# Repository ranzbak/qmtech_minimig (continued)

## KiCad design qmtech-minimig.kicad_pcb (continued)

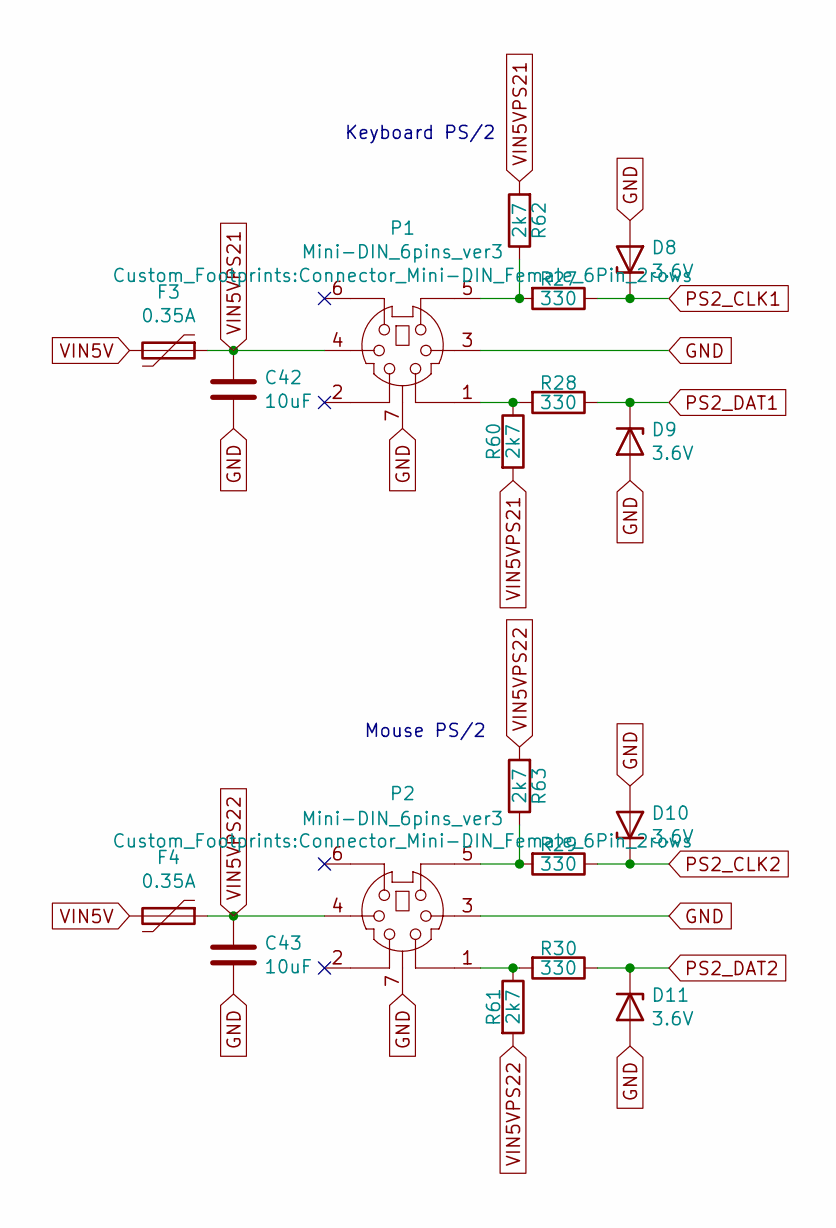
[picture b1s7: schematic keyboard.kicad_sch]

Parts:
C42, C43: 10uF; C_0805_2012Metric
D8, D9, D10, D11: 3.6V; D_SOD-323_HandSoldering
F3, F4: 0.35A; Fuse_0805_2012Metric
P1, P2: Mini-DIN_6pins_ver3; Connector_Mini-DIN_Female_6Pin_2rows
R27, R28, R29, R30: 330; R_0603_1608Metric
R60, R61, R62, R63: 2k7; R_0603_1608Metric

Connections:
unnamed: P1.1, R28.2, R60.1
unnamed: P1.5, R27.2, R62.1
unnamed: P2.1, R30.2, R61.1
unnamed: P2.5, R29.2, R63.1
PS2_CLK1: D8.1 (K), R27.1; also elsewhere on the board
PS2_CLK2: D10.1 (K), R29.1; also elsewhere on the board
PS2_DAT1: D9.1 (K), R28.1; also elsewhere on the board
PS2_DAT2: D11.1 (K), R30.1; also elsewhere on the board
VIN5V: F3.2, F4.2; also elsewhere on the board
VIN5VPS21: C42.1, F3.1, P1.4, R60.2, R62.2
VIN5VPS22: C43.1, F4.1, P2.4, R61.2, R63.2

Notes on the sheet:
Mouse PS/2
Keyboard PS/2

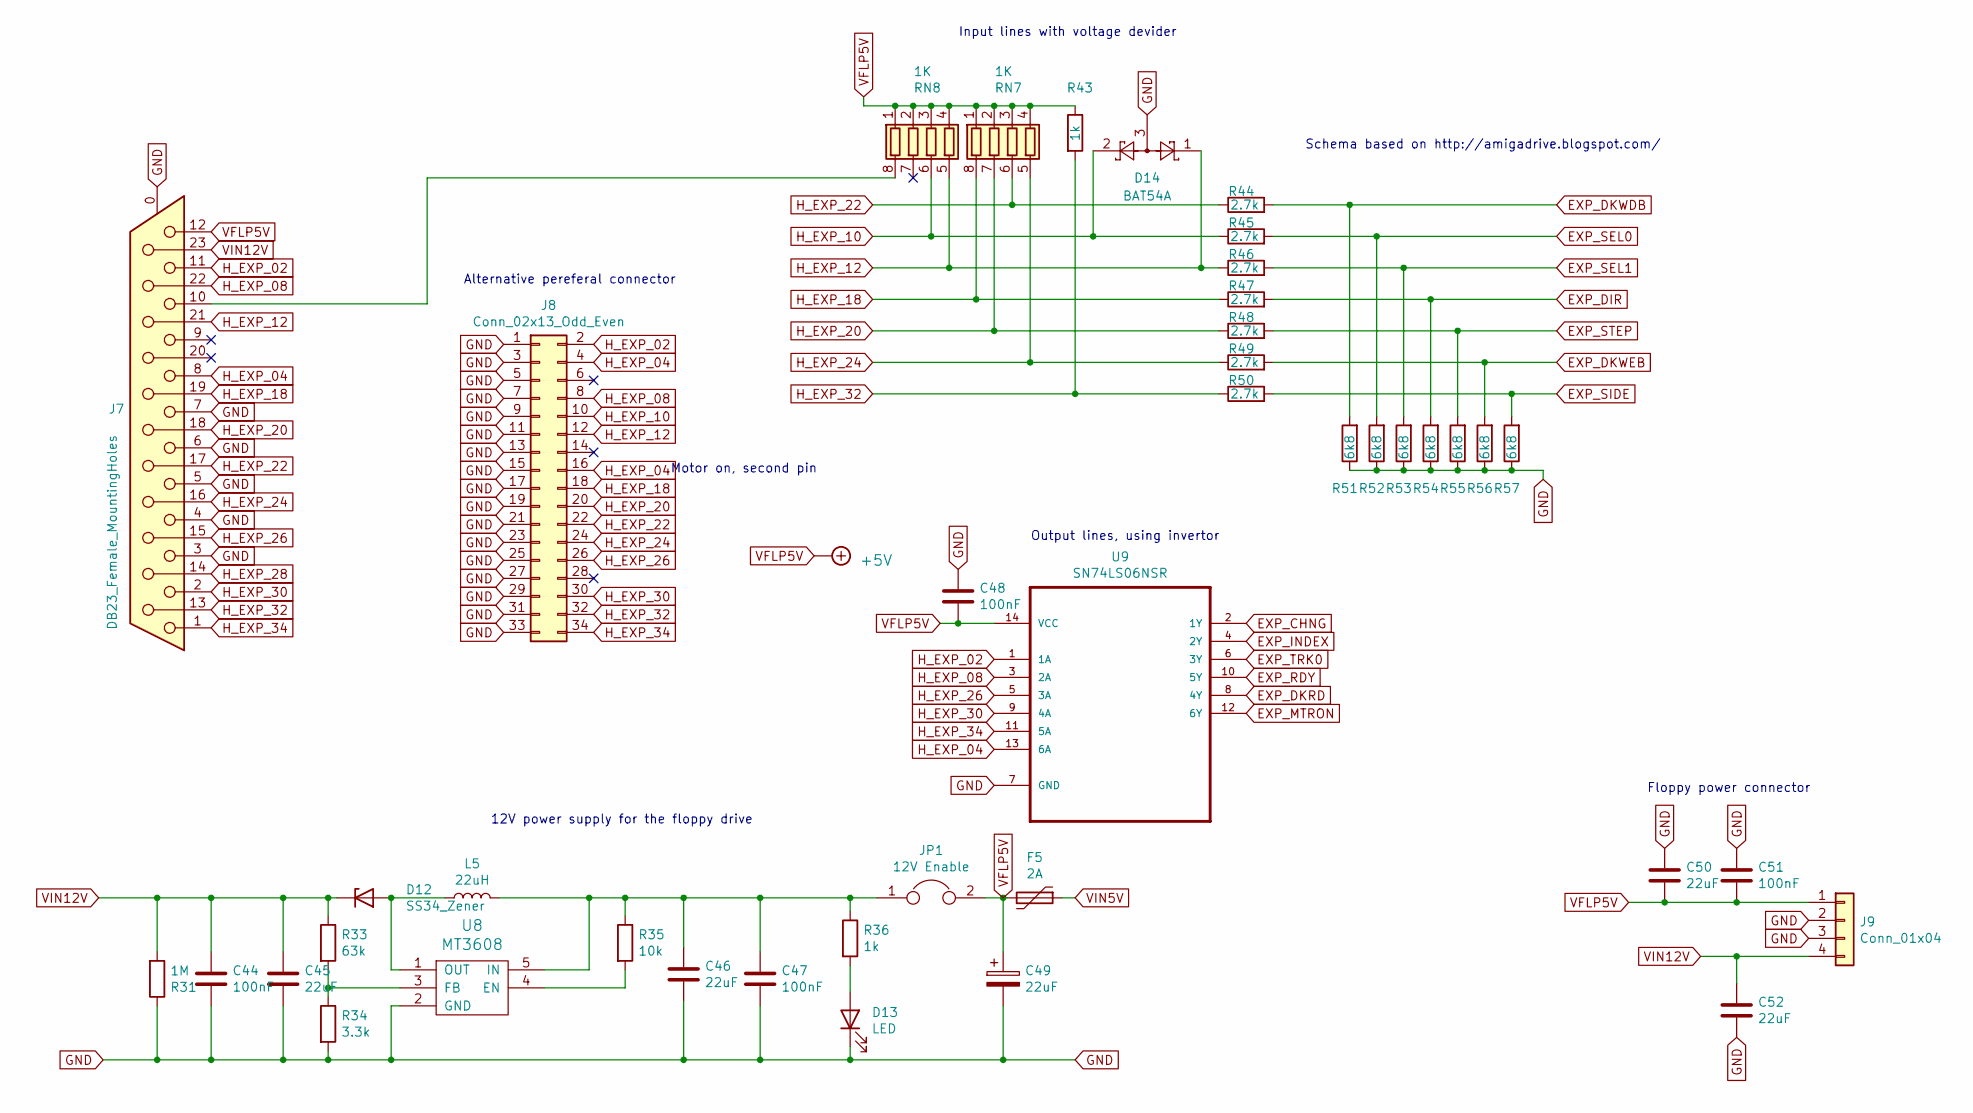
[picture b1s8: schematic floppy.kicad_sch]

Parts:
C44, C47, C48, C51: 100nF; C_0603_1608Metric
C45, C46, C50, C52: 22uF; C_0805_2012Metric
C49: 22uF; CP_Elec_5x5.4
D12: SS34_Zener; D_SMC
D13: LED; LED_0603_1608Metric
D14: BAT54A; SOT-23
F5: 2A; Fuse_0805_2012Metric
J7: DB23_Female_MountingHoles; DSUB-23_Female_Horizontal_P2.77x2.84mm_EdgePinOffset7.70mm_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
J8: Conn_02x13_Odd_Even; PinHeader_2x17_P2.54mm_Vertical
J9: Conn_01x04; JST-4-PTH-VERT
JP1: 12V Enable; PinHeader_1x02_P2.54mm_Vertical
L5: 22uH; L_10.4x10.4_H4.8
R31: 1M; R_0603_1608Metric
R33: 63k; R_0603_1608Metric
R34: 3.3k; R_0603_1608Metric
R35: 10k; R_0603_1608Metric
R36, R43: 1k; R_0603_1608Metric
R44, R45, R46, R47, R48, R49, R50: 2.7k; R_0603_1608Metric
R51, R52, R53, R54, R55, R56, R57: 6k8; R_0603_1608Metric
RN7, RN8: 1K; R_Array_Convex_4x0603
U8: MT3608; SOT-23-6
U9: SN74LS06NSR; SOIC127P780X200-14N

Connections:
EXP_CHNG: U9.2 (1Y); also elsewhere on the board
EXP_DIR: R47.2, R54.2; also elsewhere on the board
EXP_DKRD: U9.8 (4Y); also elsewhere on the board
EXP_DKWDB: R44.2, R51.2; also elsewhere on the board
EXP_DKWEB: R49.2, R56.2; also elsewhere on the board
EXP_INDEX: U9.4 (2Y); also elsewhere on the board
EXP_MTRON: U9.12 (6Y)
EXP_RDY: U9.10 (5Y); also elsewhere on the board
EXP_SEL0: R45.2, R52.2; also elsewhere on the board
EXP_SEL1: R46.2, R53.2; also elsewhere on the board
EXP_SIDE: R50.2, R57.2; also elsewhere on the board
EXP_STEP: R48.2, R55.2; also elsewhere on the board
EXP_TRK0: U9.6 (3Y); also elsewhere on the board
H_EXP_02: J7.11, J8.2, U9.1 (1A)
H_EXP_04: J7.8, J8.4, J8.16, U9.13 (6A)
H_EXP_08: J7.22, J8.8, U9.3 (2A)
H_EXP_18: J7.19, J8.18, R47.1, RN7.8 (R1.2); also elsewhere on the board
H_EXP_20: J7.18, J8.20, R48.1, RN7.7 (R2.2); also elsewhere on the board
H_EXP_22: J7.17, J8.22, R44.1, RN7.6 (R3.2); also elsewhere on the board
H_EXP_24: J7.16, J8.24, R49.1, RN7.5 (R4.2); also elsewhere on the board
H_EXP_26: J7.15, J8.26, U9.5 (3A)
H_EXP_28: J7.14
H_EXP_30: J7.2, J8.30, U9.9 (4A)
H_EXP_32: J7.13, J8.32, R43.2, R50.1
H_EXP_34: J7.1, J8.34, U9.11 (5A)
unnamed: C46.1, C47.1, JP1.1, L5.2, R35.1, R36.1, U8.5 (IN)
unnamed: D12.2 (A), L5.1, U8.1 (OUT)
unnamed: D13.2 (A), R36.2
unnamed 145: J7.10, RN8.8 (R1.2); also elsewhere on the board
unnamed: R33.2, R34.1, U8.3 (FB)
unnamed: R35.2, U8.4 (EN)
VFLP5V: C48.2, C49.1, C50.2, C51.2, F5.2, J7.12, J9.1, JP1.2, R43.1, RN7.1 (R1.1), RN7.2 (R2.1), RN7.3 (R3.1), RN7.4 (R4.1), RN8.1 (R1.1), RN8.2 (R2.1), RN8.3 (R3.1), RN8.4 (R4.1), U9.14 (VCC); also elsewhere on the board
VIN5V: F5.1; also elsewhere on the board
VIN12V: C44.1, C45.1, C52.1, D12.1 (K), J7.23, J9.4, R31.2, R33.1

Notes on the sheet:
Alternative pereferal connector
Motor on, second pin
Output lines, using invertor
Floppy power connector
Input lines with voltage devider
Schema based on http://amigadrive.blogspot.com/
12V power supply for the floppy drive

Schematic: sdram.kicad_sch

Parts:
C53, C54, C56, C57, C59, C60: 100nF; C_0603_1608Metric
C55, C58, C61: 10nF; C_0603_1608Metric
C62, C63: 10uF; C_0805_2012Metric
IC1: AS4C16M16SA-6TCN; SOP80P1176X120-54N; Manufacturer_Part_Number AS4C16M16SA-6TCN; Mouser Part Number 913-4C16M16SA-6TCN

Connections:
3V3: C53.1, C54.1, C55.1, C56.1, C57.1, C58.1, C59.1, C60.1, C61.1, C62.1, C63.1, IC1.1 (VDD_1), IC1.3 (VDDQ_1), IC1.9 (VDDQ_2), IC1.14 (VDD_2), IC1.27 (VDD_3), IC1.43 (VDDQ_3), IC1.49 (VDDQ_4); also elsewhere on the board
SDRAM_A0: IC1.23 (A0); also elsewhere on the board
SDRAM_A1: IC1.24 (A1); also elsewhere on the board
SDRAM_A2: IC1.25 (A2); also elsewhere on the board
SDRAM_A3: IC1.26 (A3); also elsewhere on the board
SDRAM_A4: IC1.29 (A4); also elsewhere on the board
SDRAM_A5: IC1.30 (A5); also elsewhere on the board
SDRAM_A6: IC1.31 (A6); also elsewhere on the board
SDRAM_A7: IC1.32 (A7); also elsewhere on the board
SDRAM_A8: IC1.33 (A8); also elsewhere on the board
SDRAM_A9: IC1.34 (A9); also elsewhere on the board
SDRAM_A10: IC1.22 (A10/AP); also elsewhere on the board
SDRAM_A11: IC1.35 (A11); also elsewhere on the board
SDRAM_A12: IC1.36 (A12); also elsewhere on the board
SDRAM_BA0: IC1.20 (BA0); also elsewhere on the board
SDRAM_BA1: IC1.21 (BA1); also elsewhere on the board
SDRAM_CAS: IC1.17 (CAS#); also elsewhere on the board
SDRAM_CKE: IC1.37 (CKE); also elsewhere on the board
SDRAM_CLK: IC1.38 (CLK); also elsewhere on the board
SDRAM_CS: IC1.19 (CS#); also elsewhere on the board
SDRAM_D0: IC1.2 (DQ0); also elsewhere on the board
SDRAM_D1: IC1.4 (DQ1); also elsewhere on the board
SDRAM_D2: IC1.5 (DQ2); also elsewhere on the board
SDRAM_D3: IC1.7 (DQ3); also elsewhere on the board
SDRAM_D4: IC1.8 (DQ4); also elsewhere on the board
SDRAM_D5: IC1.10 (DQ5); also elsewhere on the board
SDRAM_D6: IC1.11 (DQ6); also elsewhere on the board
SDRAM_D7: IC1.13 (DQ7); also elsewhere on the board
SDRAM_D8: IC1.42 (DQ8); also elsewhere on the board
SDRAM_D9: IC1.44 (DQ9); also elsewhere on the board
SDRAM_D10: IC1.45 (DQ10); also elsewhere on the board
SDRAM_D11: IC1.47 (DQ11); also elsewhere on the board
SDRAM_D12: IC1.48 (DQ12); also elsewhere on the board
SDRAM_D13: IC1.50 (DQ13); also elsewhere on the board
SDRAM_D14: IC1.51 (DQ14); also elsewhere on the board
SDRAM_D15: IC1.53 (DQ15); also elsewhere on the board
SDRAM_DQMH: IC1.39 (UDQM); also elsewhere on the board
SDRAM_DQML: IC1.15 (LDQM); also elsewhere on the board
SDRAM_RAS: IC1.18 (RAS#); also elsewhere on the board
SDRAM_WE: IC1.16 (WE#); also elsewhere on the board

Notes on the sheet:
Return path decoupling

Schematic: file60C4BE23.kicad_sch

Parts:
BT1: Battery_Cell_CR2032; BatteryHolder_Keystone_1060_1x2032
C64: 100n; C_0603_1608Metric
D15: BAT54C; SOT-23
R64: 10k; R_0603_1608Metric
U10: PCF2123TS_1,118; NXP_Semiconductors-SOT402-1-02_2016-0-*; mouser part number 771-PCF2123TS/1-T; digikey description IC RTC CLK/CALENDAR SPI 14-TSSOP
Y1: 32.768kHz; CM7VT1A32768k125pF20PPMTBQA

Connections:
unnamed: BT1.2 (-), C64.1, U10.7 (VSS)
unnamed: C64.2, D15.3, R64.1, U10.14 (VDD)
unnamed: R64.2, U10.13 (CLKOUT)
unnamed: U10.1 (OSCI), Y1.1
unnamed: U10.2 (OSCO), Y1.2

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
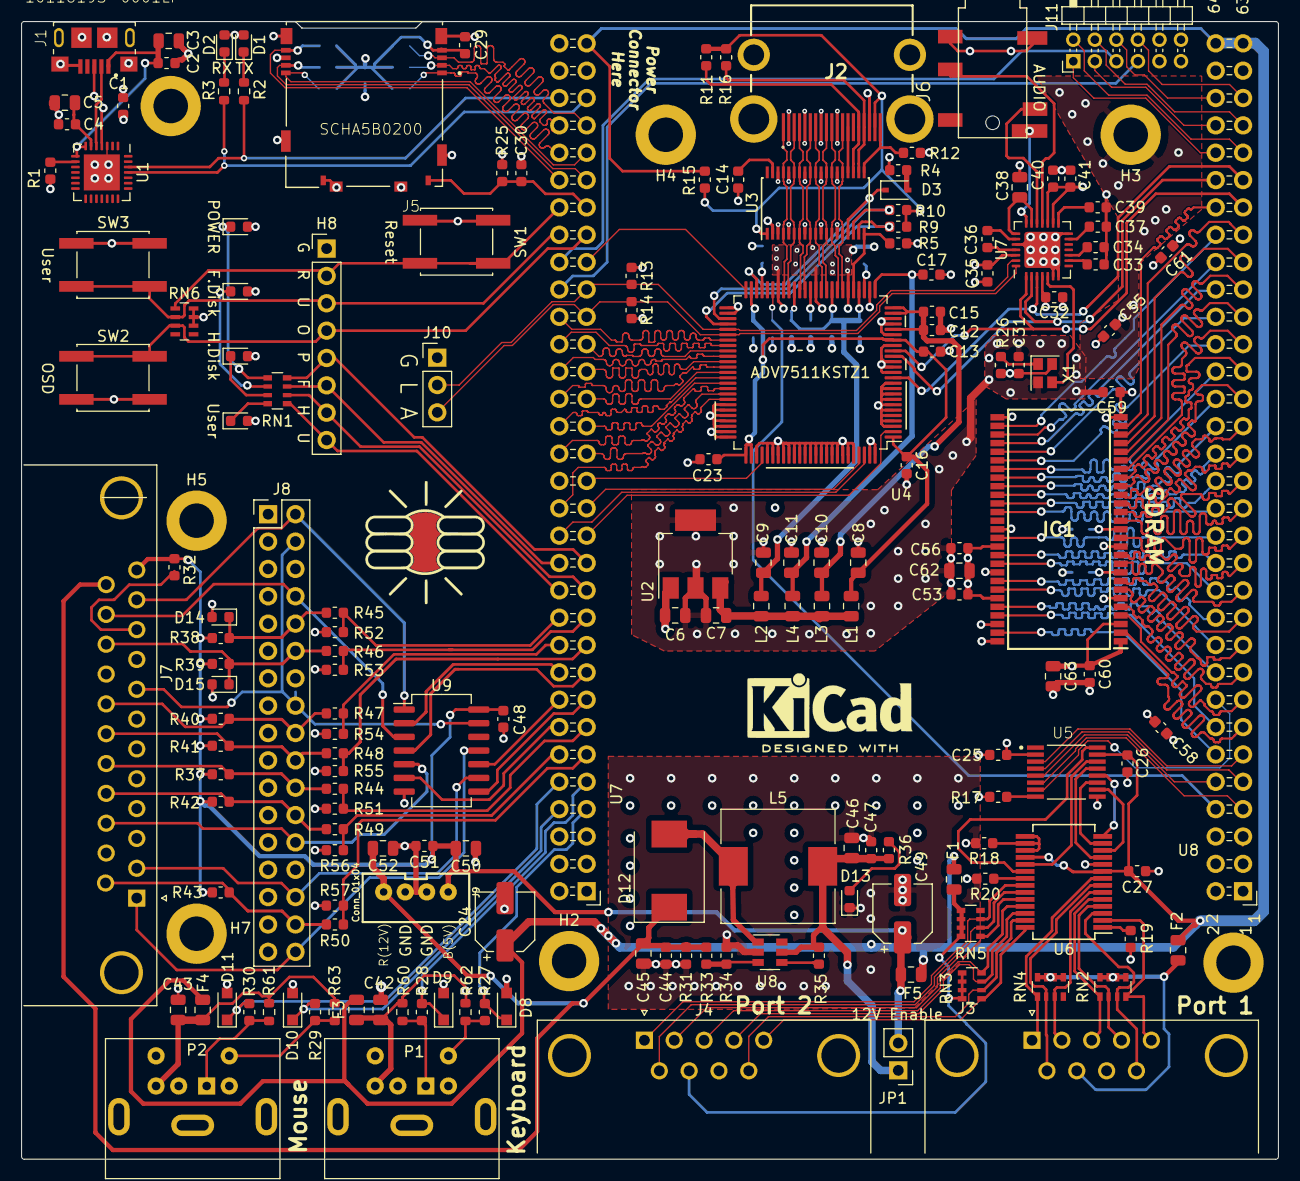
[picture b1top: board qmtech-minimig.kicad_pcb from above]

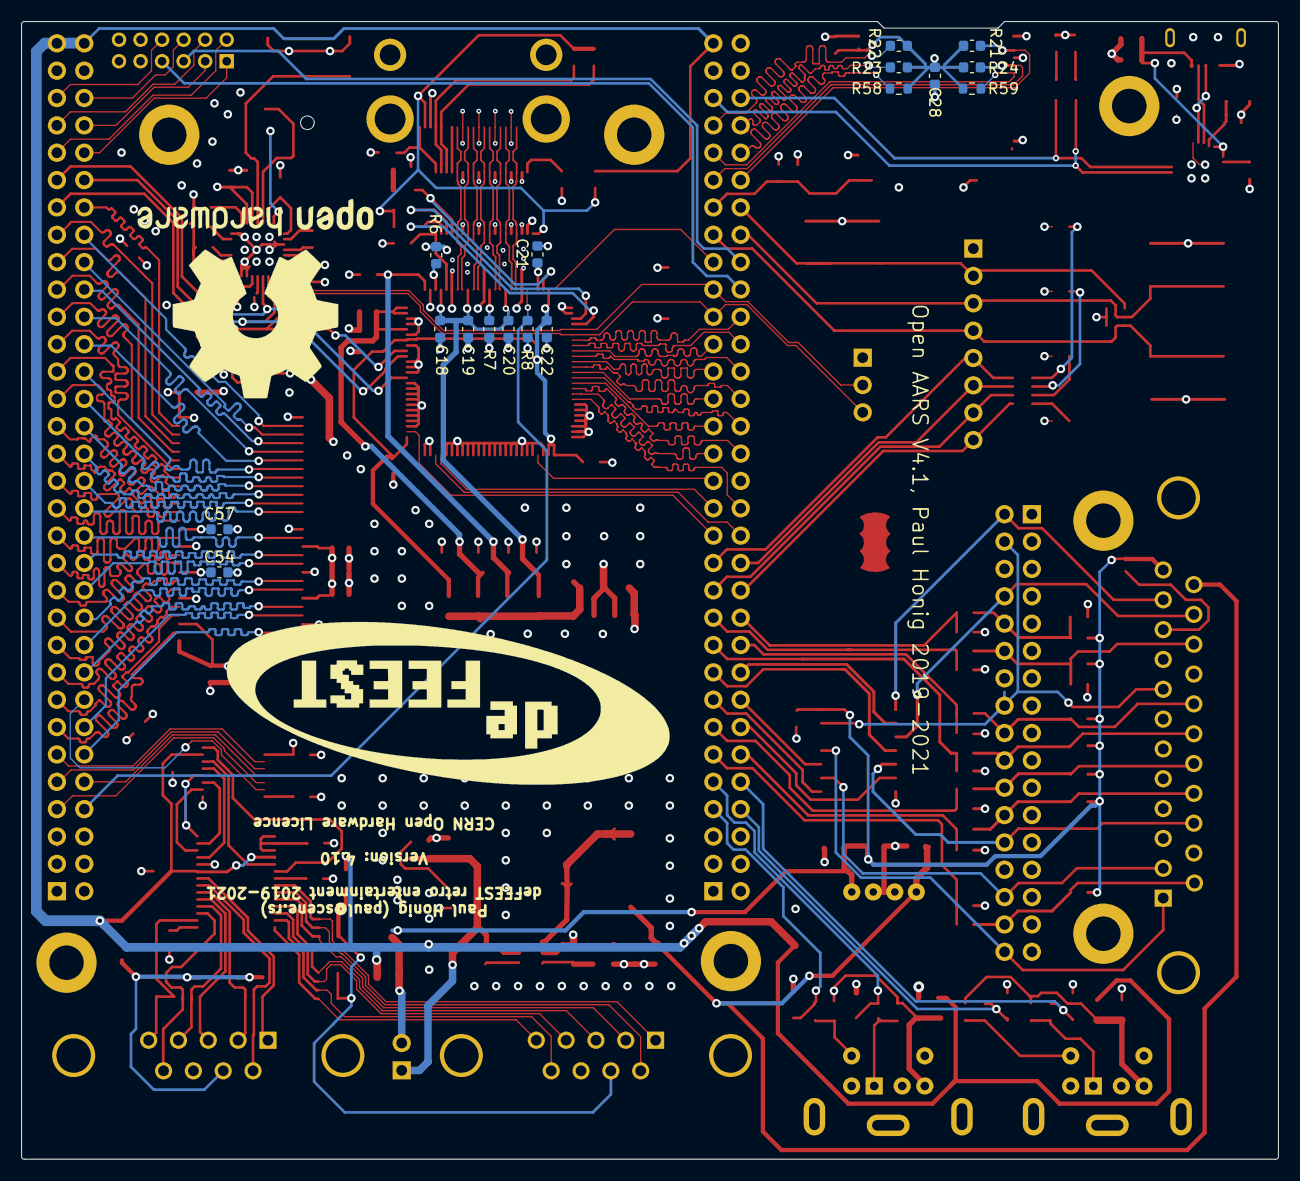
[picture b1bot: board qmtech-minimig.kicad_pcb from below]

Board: 4 copper layers, 116.7 x 105.7 mm, 194 parts (17 on the bottom side), 212 nets.

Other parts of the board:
J11: Conn_02x06_Counter_Clockwise; PinHeader_2x06_P2.00mm_Horizontal
R15: 10k; R_0603_1608Metric
R32, R37, R38, R39, R40, R41, R42: 1k; R_0603_1608Metric

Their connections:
3V3: J11.6, J11.7; also elsewhere on the board
H_EXP_18: R40.2; also elsewhere on the board
H_EXP_20: R41.2; also elsewhere on the board
H_EXP_22: R37.2; also elsewhere on the board
H_EXP_24: R42.2; also elsewhere on the board
unnamed 145: R32.2; also elsewhere on the board
PMOD_1: J11.1; also elsewhere on the board
PMOD_2: J11.2; also elsewhere on the board
PMOD_9: J11.9; also elsewhere on the board
PMOD_10: J11.10; also elsewhere on the board
PMOD_11: J11.11; also elsewhere on the board
PMOD_12: J11.12; also elsewhere on the board
VFLP5V: R32.1, R37.1, R38.1, R39.1, R40.1, R41.1, R42.1; also elsewhere on the board
VIN5V: R15.1; also elsewhere on the board

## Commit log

2019-09-02 First checkin of work in progress minimig PCB.
2019-09-02 Wired the RTL8211EG more.
2019-09-03 Fixed wiring ad7511 and wired the rtl8211EG IC
2019-09-05 Moved to full size HDMI.
2019-09-05 Added protection diodes to the joystick ports.
2019-09-05 Added Control and audio lines to the ADV7511
2019-09-05 Removed edge that should not have been there.
2019-09-07 Fixed connections for the adv7511. Fixed some minor footprint issues with the fpga board footprint.
2019-09-08 Connected adv7511 unused inputs to ground. Added high voltage protection on PS2 port. Added indicators for the rubber glue on feet.
2019-09-09 Add some files and the plot directory to the git .gitignore.
2019-09-16 First step to implement floppy interface. ESP32 check wireing in.
2019-09-23 Integrated the Rover V2 into the board, added level shifters for the floppy interface.
2019-09-24 Moved the micro USB connector to the bottom of the board, so the D+ and D- do not have to cross to the IC.
2019-10-06 Add the External floppy interface. Routed the HDMI tracks + match impendence.
2019-10-11 Fixed HDMI Impedance to 50Ohm, 100Ohm differential, for 0.1mm bord. Add pullups to HDMI I2C, connected DE pin to FPGA.
2019-10-13 Fixed some issues with the 50 Ohm impedance of the SPI lines. Added pinout .odt.
2019-10-13 Removed an extra esp32 footprint that was outside of the design.
2019-10-13 Add rescue.lib file, so the symbols are included.
2019-10-14 Add the missing files.
2019-10-24 Added ESD protection, and removed the curved lines around the adv7511.
2019-10-29 Add an oscillator for the CEC functionality.
2019-10-31 Added mounting holes.
2019-12-03 Renamed some values for consistency
2019-12-03 LEDs
2019-12-05 Changed zener diode footprint for easy soldering. Fixed pins, U861/2 and U761/2 they now connect correctly to ground.
2019-12-24 Fixed reversed labeling of the QMTECH FPGA board pins.
2019-12-29 Changed Joystick configuration to level shifting IC.
2019-12-29 Add a basic readme to the project.
2020-01-12 Add Max9850 to handle audio.
2020-01-12 Remove .lock file ods file.
2020-01-12 Joystick port 7 is not powered at 5V, polyfuses have been added, txs0108 are used for the joystick ports.
2020-01-12 The DB9 connectors now have ground on the outer sleve.
2020-01-18 Change order of the VSPI to FPGA to make sure the clock pin connects to an FPGA clock capable pin.
2020-02-23 Add PS/2 Mouse connector to the board, USB has too much overhead.
2020-03-08 Add 3d models to most components, Add decoupling of the Line ins of the max9850. Add new defeest Logos.
2020-07-13 Minimig V2
2020-07-13 First checkin of SDRAM Open AARS board.
2020-07-13 Fixed some weird routing.
2020-07-16 Implemented the Floppy interface, fixed 12V power up issue with the board.
2020-07-16 Version that was sent to JLCPCB 20200716.
2020-07-18 Fixed SDRAM_A12 missing route, disconnected JS_INT_B.
2020-07-27 Fixed I2C pullup resistors.
2020-09-27 Add footprints in Library. Add picture of the finished board in README.
2020-09-29 Fixed regression from an earlier pin numbering mistake. Changed Joystick pullups for resistor network.
2020-09-30 Fixed some external dependencies.
2020-09-30 Update README with disclaimer.
2020-09-30 Revert "Fixed some external dependencies."
    This reverts commit ddca1efdf68af69ddd54947bcdaa3cfa1d913e0d.
2020-09-30 Fixed Missing PCB logos.
2020-10-01 First setup of board with better IO distribution for the FPGA
2020-10-01 Fix missing resistor array.
2020-10-05 Wired up the adv7511
2020-10-06 Removed all libraries that depend on absolute paths.
2020-10-06 Did some placement to make the PCB smaller.
2020-10-09 First rough version of the Open AARS V4
2020-10-10 Fixed issues with V4 board, length matching, region matching, footprints, symbols.
2020-10-26 Brought compenents back to the front for easy soldering.
2020-10-29 Removed ESP32, as it's no longer needed, we have soft cores.
2020-10-30 Fixed a bunch of small issues.
2020-11-05 open changes.
2020-11-06 Connect I2S to both Max9850 and ADV7511.
2020-11-24 Fixed the position of some labels, that were under components.
2020-12-21 Fixed decoupling of VDD SDRAM, fixed pinout error in V4 board pinout sheet.
2021-03-10 Fixed issue with missing PS2 pullups, add line to adv interrupt.
2021-03-23 Add notch for audio plug.
2021-03-25 Add Audio jack cut out. Update documentation. fix minor issues in the layout.
2021-06-12 Add project files
2021-11-30 Add link to firmware repo
2022-05-22 Remove kicad 5 files, add kicad 6 files.
2022-07-19 Fixed board for Kicad 6, replaced some missing footprints.
2023-03-10 Convert to Kicad 7.0
2023-03-21 Prod version of OpenAARS 5.0 design.
2023-03-26 V5 Version of the board.
